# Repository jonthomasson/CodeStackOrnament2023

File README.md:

# CodeStack Team C 2023 Christmas Ornament Project

## Overview

Welcome to the CodeStack Team C Christmas Ornament project! This isn't just any holiday decoration; it's a geeky masterpiece designed by developers for developers. Embodying the spirit of CodeStack, this unique ornament is a playful blend of electronics and a bit of geek culture, perfect for those who appreciate the quirks of digital logic and binary systems, which at its core are the systems which run our code!

### Circuit Description

Our circuit is centered around the 555 timer IC, configured in astable mode to generate a 4Hz timing signal, which feeds into a CD74HC4040 binary counter. The output from this binary counter powers 12 LEDs arranged around the PCB in a binary sequence.

#### Binary Counter and LED Display

At the core of our ornament is the CD74HC4040 binary counter. Unlike traditional LED displays, this counter follows a binary sequence, lighting up LEDs in a pattern that reflects binary counting principles.

#### Reset Circuit

We've included a reset circuit using the TPS3840PH for a consistent experience. This setup ensures that the binary counter starts at zero every time the ornament is powered up. A manual reset button is also provided for added user control.

## Embracing the Geekiness

This ornament is a nod to our geeky nature at CodeStack. It's designed to intrigue and amuse, combining fundamental electronics with a bit of developer humor. It's more than just a festive decoration; it's a representation of our love for coding, circuitry, and all things geeky.

## Binary Counting Explained

This ornament is a hands-on lesson in binary counting. The binary counter ranges from 0 to 4096, with each LED representing a binary power:

- 1, 2, 4, 8, 16, 32, 64, 128, 256, 512, 1024, and 2048.

As the counter advances, the corresponding LEDs light up. To find the current count, simply add the values of all illuminated LEDs. It's a delightful way to visualize how binary numbers work! Below is a representation of how the process of counting in binary works:

## A Festive Joke

At first glance, it might just seem like an oddly blinking LED ornament. But in true CodeStack fashion, there's more than meets the eye. It's a playful demonstration of binary counting, making it not just a decoration, but a conversation piece about digital electronics and our geeky passions.

## Conclusion

Embrace your inner geek! This project aims to be a testament to our love for technology, coding, and a bit of festive fun. Enjoy this unique blend of holiday cheer and geek culture!

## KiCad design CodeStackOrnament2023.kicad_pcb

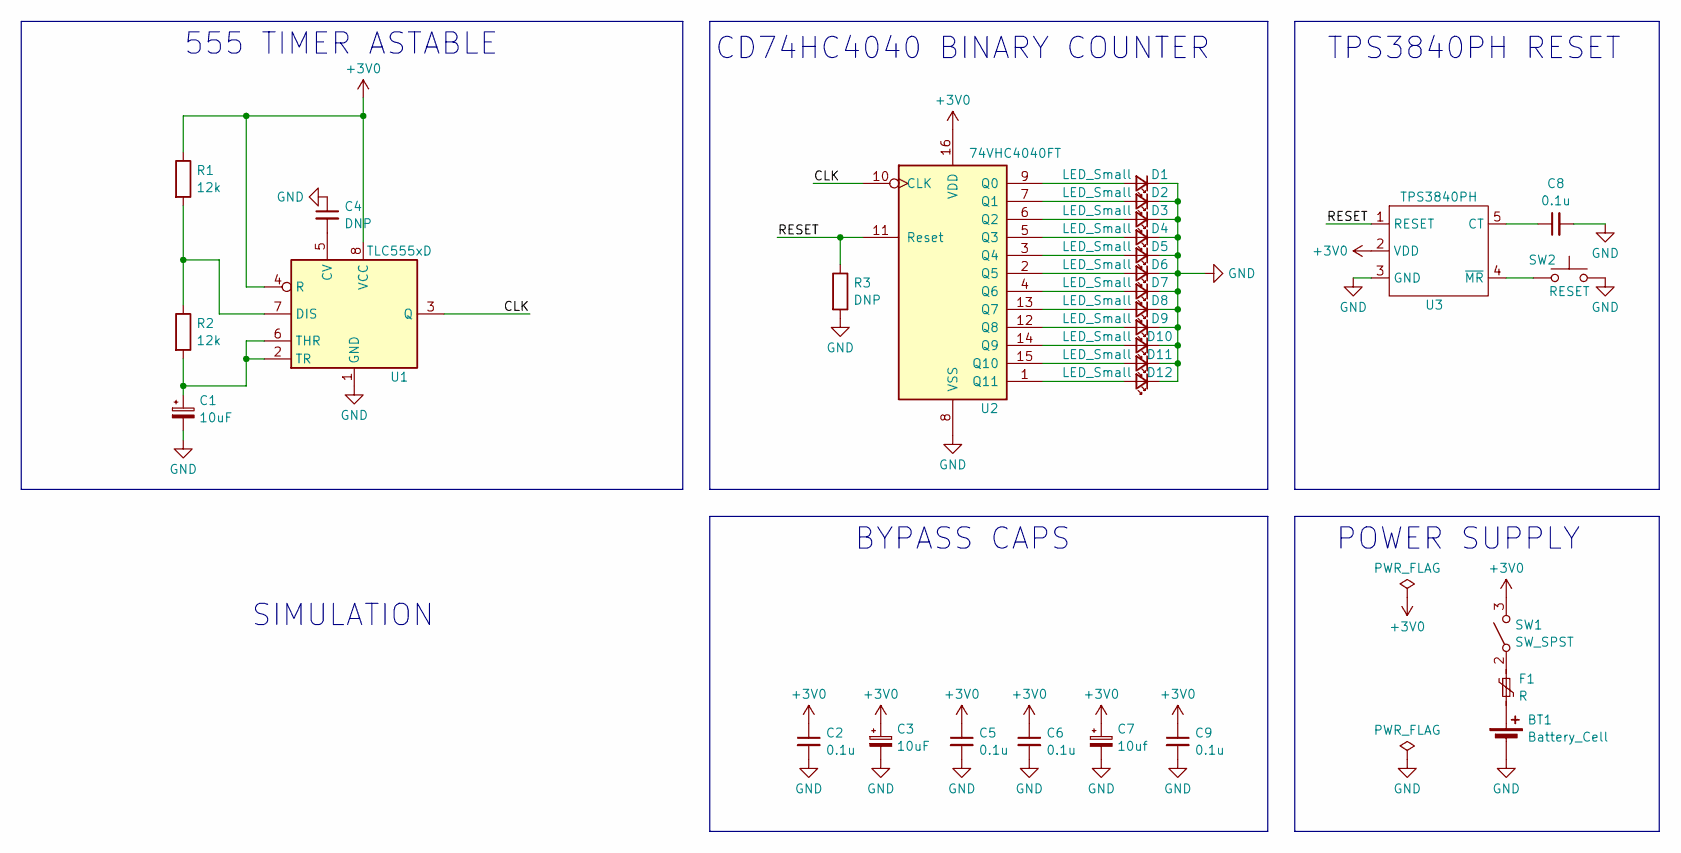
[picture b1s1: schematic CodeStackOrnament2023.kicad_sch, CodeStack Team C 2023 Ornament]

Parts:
BT1: Battery_Cell; BAT_2468
C1, C3: 10uF; C_0805_2012Metric
C2, C5, C6, C8, C9: 0.1u; C_0805_2012Metric
C4: DNP; C_0805_2012Metric
C7: 10uf; C_0805_2012Metric
D1, D2, D3, D4, D5, D6, D7, D8, D9, D10, D11, D12: LED_Small; 156120RS75300_LED
F1: R; SMD1206B050TF_FUSE
R1, R2: 12k; R_0805_2012Metric
R3: DNP; R_0805_2012Metric
SW1: SW_SPST; JS202011SCQN_SWITCH
SW2: RESET; PTS815_SWITCH
U1: TLC555xD; TLC555_SOIC
U2: 74VHC4040FT; CD74HC4040M96_SOIC16
U3: TPS3840PH; TPS3840_RESET

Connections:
+3V0: C2.1, C3.1, C5.1, C6.1, C7.1, C9.1, R1.1, SW1.3 (B), U1.4 (R), U1.8 (VCC), U2.16 (VDD), U3.2 (VDD)
/CLK: U1.3 (Q), U2.10 (CLK)
/RESET: R3.1, U2.11 (Reset), U3.1 (RESET)
GND: BT1.2 (-), C1.2, C2.2, C3.2, C4.1, C5.2, C6.2, C7.2, C8.2, C9.2, D1.1 (K), D2.1 (K), D3.1 (K), D4.1 (K), D5.1 (K), D6.1 (K), D7.1 (K), D8.1 (K), D9.1 (K), D10.1 (K), D11.1 (K), D12.1 (K), R3.2, SW2.4, U1.1 (GND), U2.8 (VSS), U3.3 (GND)
unnamed: BT1.1 (+), F1.2
unnamed: D1.2 (A), U2.9 (Q0)
unnamed: D2.2 (A), U2.7 (Q1)
unnamed: D3.2 (A), U2.6 (Q2)
unnamed: D4.2 (A), U2.5 (Q3)
unnamed: D5.2 (A), U2.3 (Q4)
unnamed: D6.2 (A), U2.2 (Q5)
unnamed: D7.2 (A), U2.4 (Q6)
unnamed: D8.2 (A), U2.13 (Q7)
unnamed: D9.2 (A), U2.12 (Q8)
unnamed: D10.2 (A), U2.14 (Q9)
unnamed: D11.2 (A), U2.15 (Q10)
unnamed: D12.2 (A), U2.1 (Q11)
unnamed: F1.1, SW1.2 (A)
unnamed: C4.2, U1.5 (CV)
unnamed: R1.2, R2.1, U1.7 (DIS)
unnamed: C1.1, R2.2, U1.2 (TR), U1.6 (THR)
unnamed: C8.1, U3.5 (CT)
unnamed: SW2.1, U3.4 (~MR)

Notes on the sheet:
BYPASS CAPS
TPS3840PH RESET
SIMULATION
POWER SUPPLY
CD74HC4040 BINARY COUNTER
555 TIMER ASTABLE

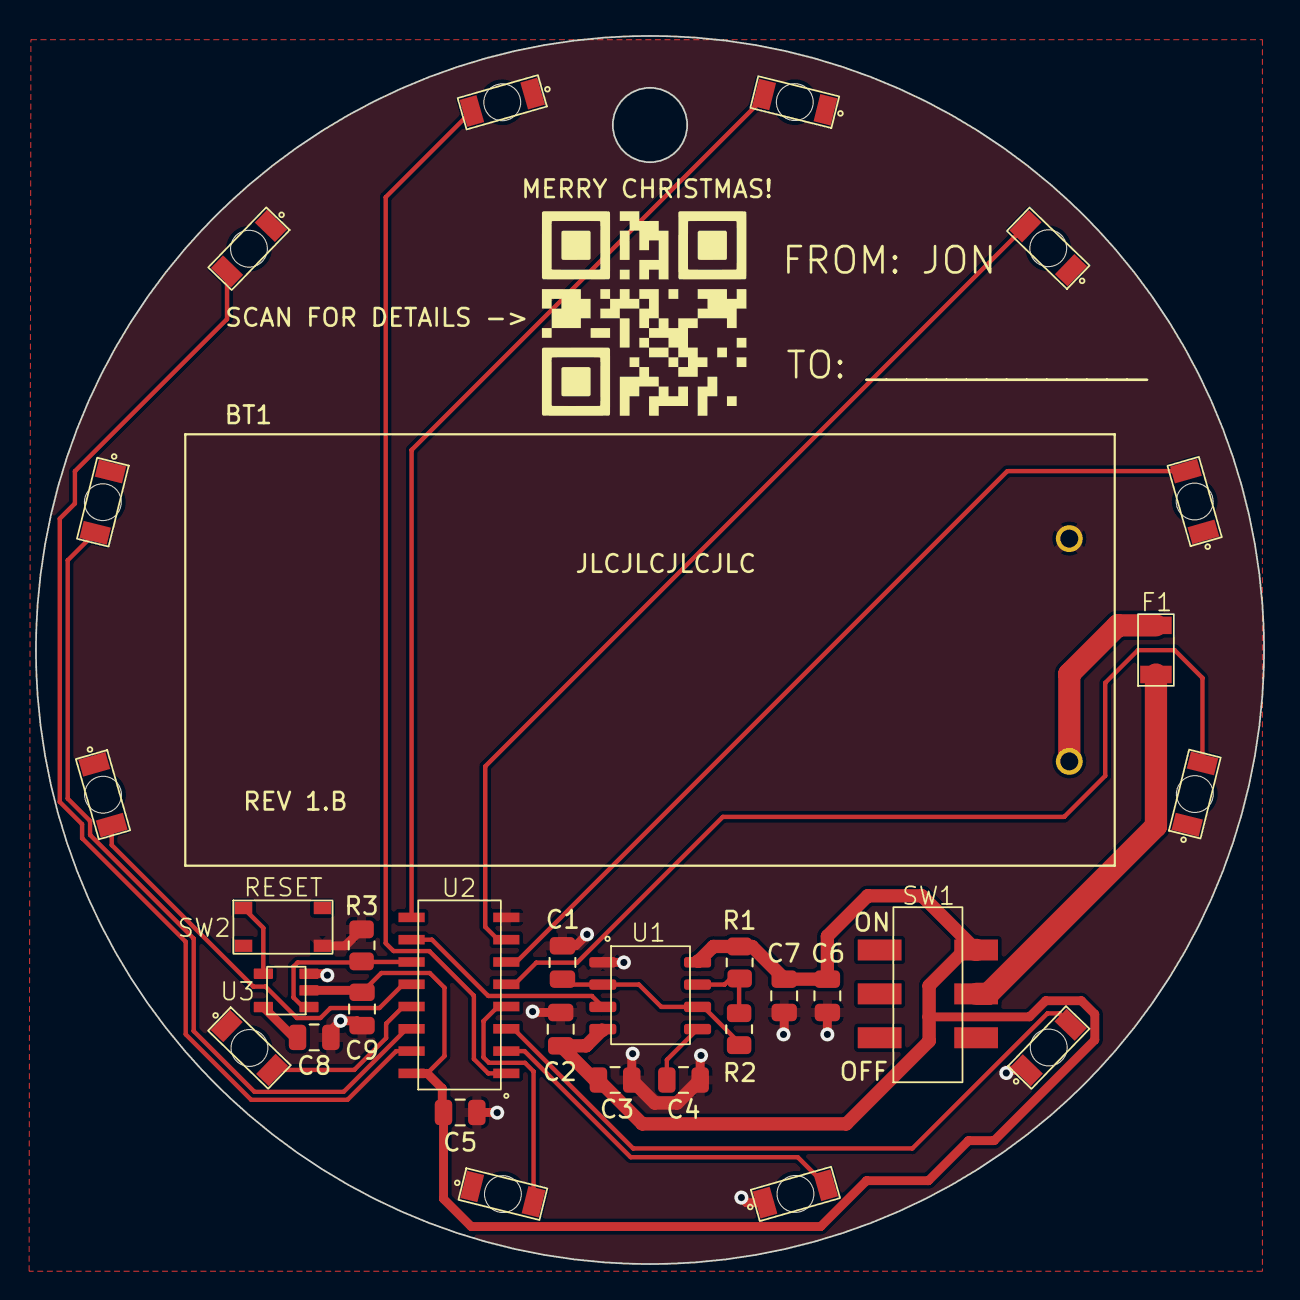
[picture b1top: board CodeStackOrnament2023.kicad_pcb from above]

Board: 2 copper layers, 70.0 x 70.0 mm, 31 parts (0 on the bottom side), 23 nets.

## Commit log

2023-10-12 initial checkin
2023-10-13 adding battery and boost circuit
2023-10-16 finishing schematic. starting on footprints.
2023-10-17 adding switch footprint and model
2023-10-18 adding footprint for battery holder
2023-10-20 refactoring power
2023-10-22 spice and footprint models. refactoring power supply.
2023-10-23 starting board design
2023-10-24 updating footprints
2023-10-24 board layout
2023-10-24 starting board routing
2023-10-25 more routing
2023-10-25 more routing and layout
2023-10-25 Finishing routing.
2023-10-26 increasing board size a bit.
2023-10-28 adding codestack solder mask logo
2023-10-28 updating silkscreen
2023-10-28 adjusting codestack logo on solder mask
2023-10-29 silkscreen logos
2023-10-29 adding qr code and a few more logos for silkscreen.
2023-10-30 fixing drc
2023-10-30 fixing last drc
2023-10-30 aligning silkscreen
2023-10-30 more alignment with u2
2023-10-31 adding gerbers
2023-11-05 adding gerbers. cleaning up schematic.
2023-11-11 starting rev 1.b with added reset circuitry.
2023-11-11 rev 1.b adding footprints
2023-11-12 finshed routing rev 1.b with reset circuit
2023-11-19 rev 1.b added a reset circuit to ensure counter starts at 0. Reorganizing schematic.
2023-12-08 adding pics of finished board and schematic
    adding pics of finished board and schematic.
